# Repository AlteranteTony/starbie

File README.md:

# starbie
a fun  little pet !

starbie isa cute fun little  interactive digital pet
this project includes a custom digital pet - which i named LEgoat

starbie uses parts such as esp32-c3 , switches , resistor , MPU6050 module ,an oled screen and a DHT11 sensor.

# What does starbie do:
Starbie is a cute interactive desk pet that reacts to you and your surroundings.
it is a small digital pet (LEgoat) that has 2 buttons and mpu6050 module , the mpu6050 module helps it make reactive to tilting and shaking .

what is in the repo
- starbie.ino this includes the code
-BOM.md it contins bill of materials
-journal.md contains journal that i wrote while working on starbie
-project file - pcb layout , circuit design
-production 1 contains files for fabrication of pcb

## Tech stack
- kicad
- c++
- arduino ide

how to set up firmware ( use arduino ide)
-open the firmware folder. install listed libraries now select xiao esp32 c3 board and the correct port and upload the code. after that you are basically good to go.

## How to Use starbie

### Controls

- Button 1 =it  Opens the action menu and confirms a selected action.
- Button 2 = Toggles the stats screen.
- Shake = Give LEgoat a small joy boost.

### Actions
the starbie has actions like nap , play , feed , laugh . laugh action makes LEgoat jump and show ha ha text. when you use Feed it gains fullness . when using play runs around the screen and gains joy . Nap it goes to sleep.

Stats range from 0 to 100 

### Sensors use in project

The MPU6050 detects movement and controls the action menu. The DHT11 measures temperature and humidity, which are displayed on the stats screen.

YOU CAN CUSTOMIZE THE PET IF YOU WANT !!

PCB WAS CHECKED FOR ERRORS USING KI CAD'S DRC. CHECK PCB FOR ERROR BEFORE MANUFACTURING THE PCB 

FINAL LOOK FOR PCB

3D render of PCB

## Bill of Materials (BOM)

The following components are used to build Starbie.

| Designator | Footprint | Quantity | Value | vendor name | Unit Price ($) | Line Total ($) | Link |
|---|---|---:|---|---|---:|---:|---|
| J1 | Display_128x64_096_I2C | 1 | Conn_01x04_Pin | Sharvi electronics | 2.17 | 2.17 | https://sharvielectronics.com/product/0-96-inch-i2c-4pin-oled-display-module-white/ |
| J2 | MPU6050_Module | 1 | Conn_01x08_Pin | Sharvi electronics | 1.95 | 1.95 | https://sharvielectronics.com/product/mpu-6050-3-axis-accelerometer-and-gyro-sensor/ |
| R1 | R_Axial_DIN0207_L6.3mm_D2.5mm_P7.62mm_Horizontal | 1 | 10K | Sharvi electronics | 0.26 | 0.26 | https://sharvielectronics.com/product/10k-ohm-1-2-watt-resistor-1-tolerance/ |
| SW1, SW2 | SW_Cherry_MX_1.00u_PCB | 2 | SW_Push | Sunrom electronics | 1.2 | 2.40 | https://www.sunrom.com/m/6479 |
| U1 | XIAO-ESP32-C6-DIP | 1 | XIAO-ESP32-C3-SMD | Sharvi electronics | 6.56 | 6.56 | https://sharvielectronics.com/product/seeed-studio-xiao-esp32c3-tiny-mcu-board-with-wifi-and-ble-battery-charge-supported-module/ |
| U2 | Aosong_DHT11_5.5x12.0_P2.54mm | 1 | DHT11 | Sharvi electronics | 0.71 | 0.71 | https://sharvielectronics.com/product/dht11-temperature-and-humidity-sensor-module/ |
| N/A | PCB | 1 | - | JLCPCB | 10 | 10 | https://jlcpcb.com/ |
| | | | | TOTAL= | $24.5 | | |

*Prices are estimates and may change. Shipping, taxes, and other charges may not be included.*

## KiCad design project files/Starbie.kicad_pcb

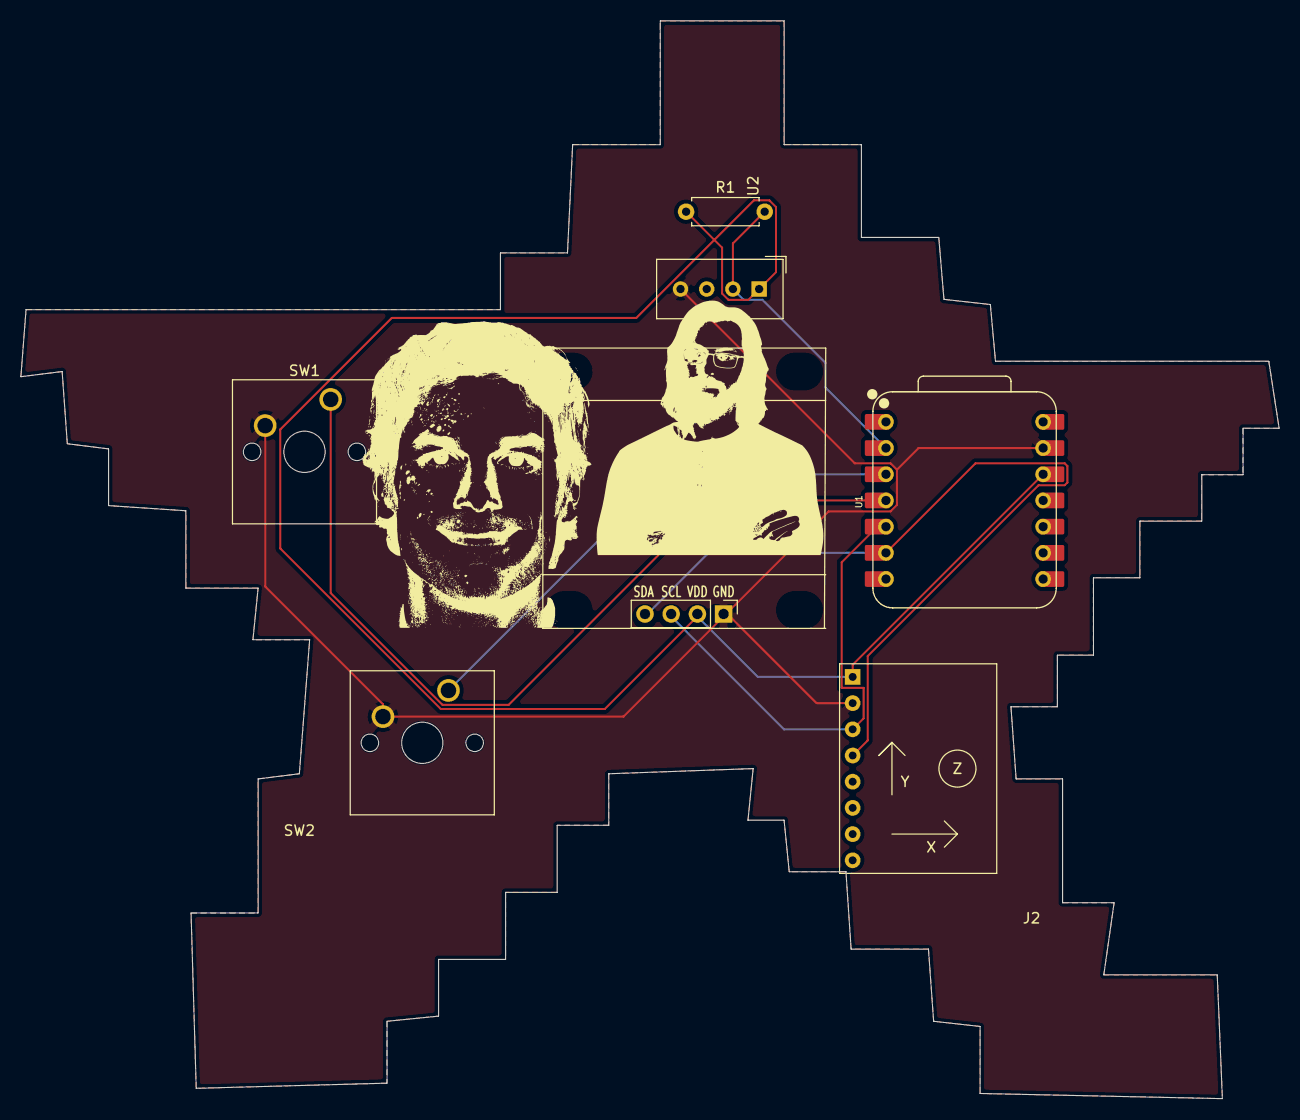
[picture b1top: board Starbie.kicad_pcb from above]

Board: 2 copper layers, 122.0 x 104.5 mm, 7 parts (0 on the bottom side), 7 nets.

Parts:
J1: Conn_01x04_Pin; Display_128x64_096_I2C
J2: Conn_01x08_Pin; MPU6050_Module
R1: 10K; R_Axial_DIN0207_L6.3mm_D2.5mm_P7.62mm_Horizontal
SW1, SW2: SW_Push; SW_Cherry_MX_1.00u_PCB
U1: XIAO-ESP32-C3-SMD; XIAO-ESP32-C6-DIP
U2: DHT11; Aosong_DHT11_5.5x12.0_P2.54mm

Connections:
+3.3V: J1.2, J2.1, R1.1, U1.12 (3V3_OUT), U2.1 (VDD)
/DHT11 DATA: R1.2, U1.2 (D1), U2.2 (DATA)
/GPIO2: SW2.1, U1.3 (D2)
/GPIO3: SW1.1, U1.4 (D3)
/SCL: J1.3, J2.3, U1.5 (D4)
/SDA: J1.4, J2.4, U1.6 (D5)
GND: J1.1, J2.2, SW1.2, SW2.2, U1.13 (GND), U2.4 (GND)
